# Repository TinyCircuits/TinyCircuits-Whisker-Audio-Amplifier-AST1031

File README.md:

# TinyCircuits Wireling Audio Amplifier
# AST1031 Rev2

The design files are located under design_files/ for the TinyCircuits AST1031 Rev 2 PCB. This is a Wireling board which features a Class-D audio amplifier and speaker connections to boost an audio signal to a speaker.

Format is in Cadsoft Eagle format - Eagle version 6.2 was used for the original design.

For more infomation on this, check out the product page at TinyCircuits.com

# License:

Design by TinyCircuits.
All design files are released under the Creative Commons Attribution Share-Alike 3.0 License, see the following link for details: http://creativecommons.org/licenses/by-sa/3.0

All text above must be included in any redistribution or derived design

This project uses designs and concepts developed as part of the Arduino project and the LilyPad project.  The TinyCircuits design files themselves (schematics, PCB and libraries) are not directly derived from these works' design files and have been created new, however the concepts and basic architecture behind the TinyDuino and TinyLily products are derived and we thank the hard work of the organizations below for their contributions to open-source hardware:
  
Original Arduino Uno Design by Team Arduino

LilyPad Arduino Design by Leah Buechley and Sparkfun Electronics

Please support the open-source hardware community

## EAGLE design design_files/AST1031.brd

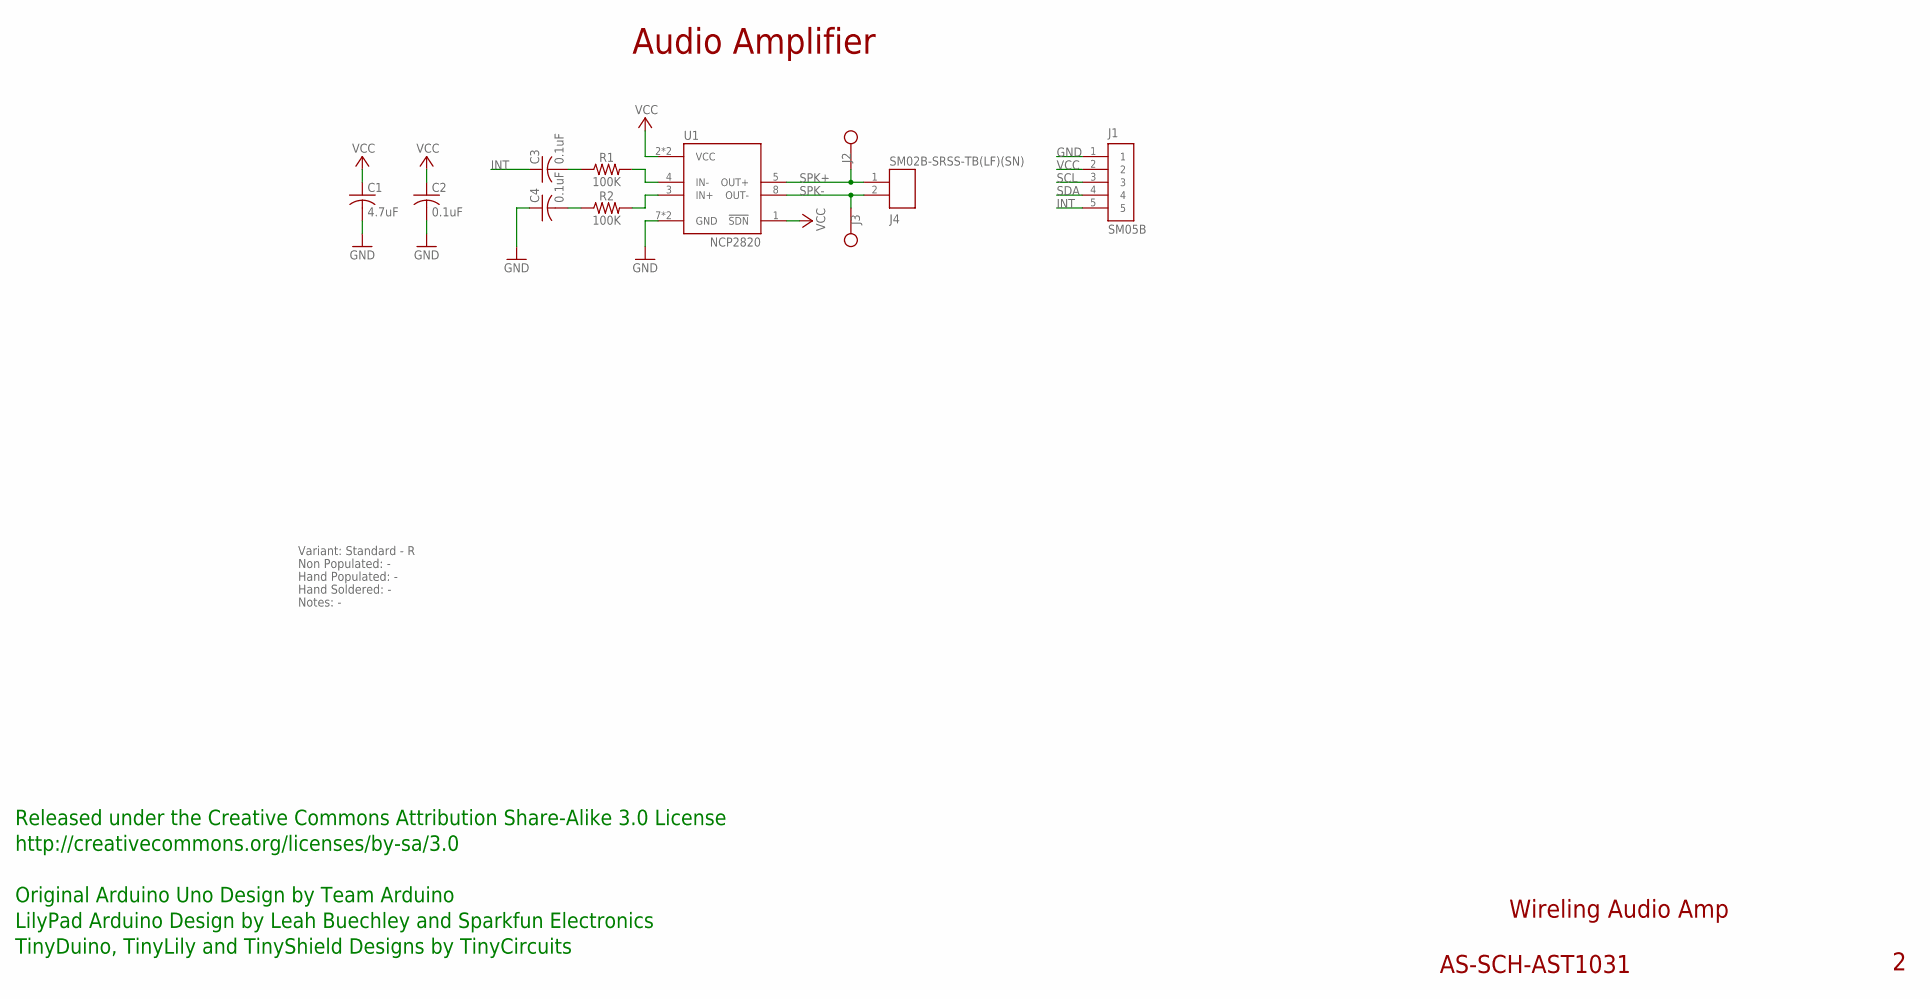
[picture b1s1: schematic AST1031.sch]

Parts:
C1: 4.7uF; C0603; PARTNO AS-ITM-00088
C2, C3, C4: 0.1uF; C0402
J1: SM05B; JST_SH_5X1_EDGE
J2, J3: 0.78MM_TH
J4: SM02B-SRSS-TB(LF)(SN); JST_SH_2X1
R1, R2: 100K; 0402
U1: NCP2820; WSON-8

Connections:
GND: C1.2, C2.2, C4.1, J1.1, U1.7 (GND), U1.9 (GND)
INT: C3.1, J1.5
unnamed: R1.2, U1.4 (IN-)
unnamed: R2.2, U1.3 (IN+)
unnamed: C3.2, R1.1
unnamed: C4.2, R2.1
SCL: J1.3
SDA: J1.4
SPK+: J2.P$1, J4.1 (2), U1.5 (OUT+)
SPK-: J3.P$1, J4.2 (1), U1.8 (OUT-)
VCC: C1.1, C2.1, J1.2, U1.1 (!SDN), U1.2 (VCC), U1.6 (VCC)

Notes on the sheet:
Wireling Audio Amp
AS-SCH-AST1031
Audio Amplifier
Released under the Creative Commons Attribution Share-Alike 3.0 License
http://creativecommons.org/licenses/by-sa/3.0
Original Arduino Uno Design by Team Arduino
TinyDuino, TinyLily and TinyShield Designs by TinyCircuits
LilyPad Arduino Design by Leah Buechley and Sparkfun Electronics
Non Populated: -
Hand Populated: -
Hand Soldered: -
Variant: Standard - R
Notes: -

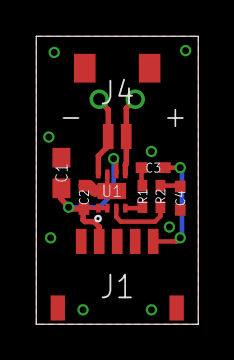
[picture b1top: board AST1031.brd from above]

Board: 2 copper layers, 9.0 x 16.0 mm, 12 parts (1 on the bottom side), 9 nets.

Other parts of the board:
U$1: DOCFIELD-TINYCIRCUITS-PCB

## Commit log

2019-09-18 schematic
2019-12-17 updated documentation
2020-02-04 mass image update
2020-08-14 Add CAD data
